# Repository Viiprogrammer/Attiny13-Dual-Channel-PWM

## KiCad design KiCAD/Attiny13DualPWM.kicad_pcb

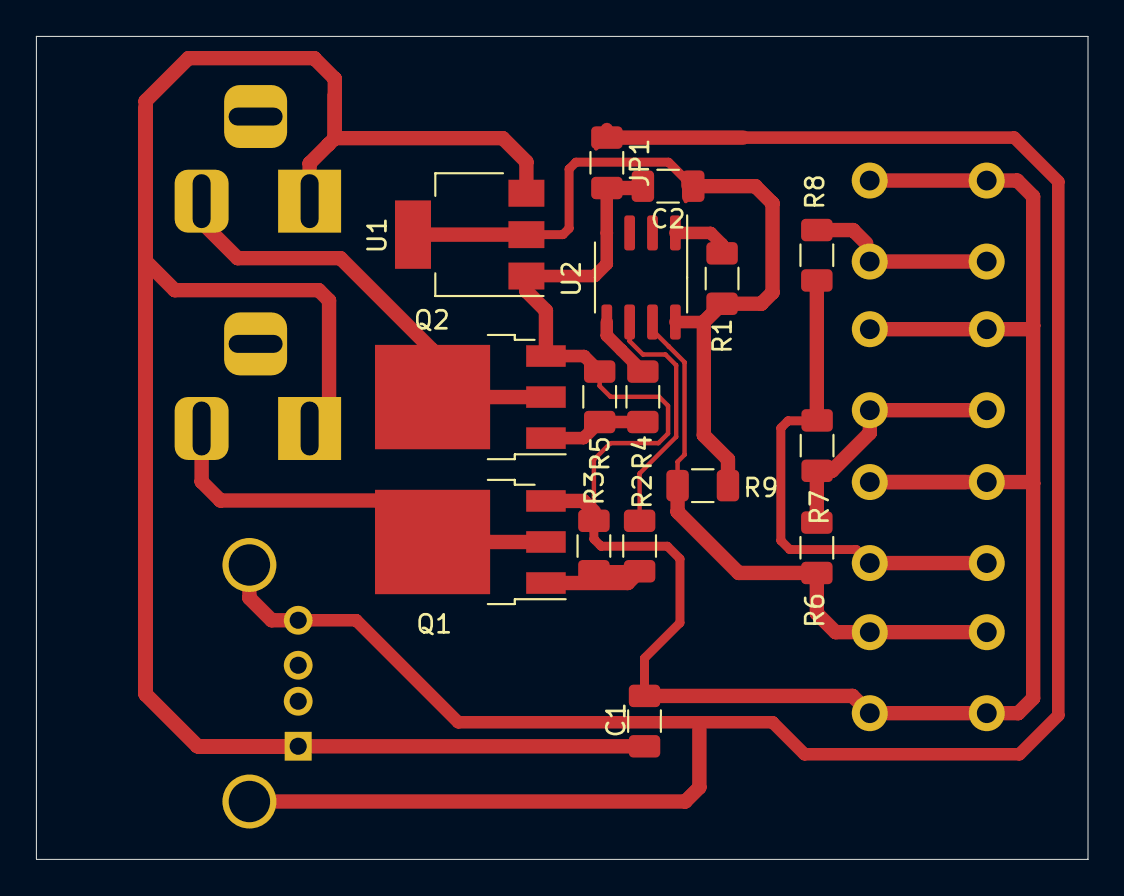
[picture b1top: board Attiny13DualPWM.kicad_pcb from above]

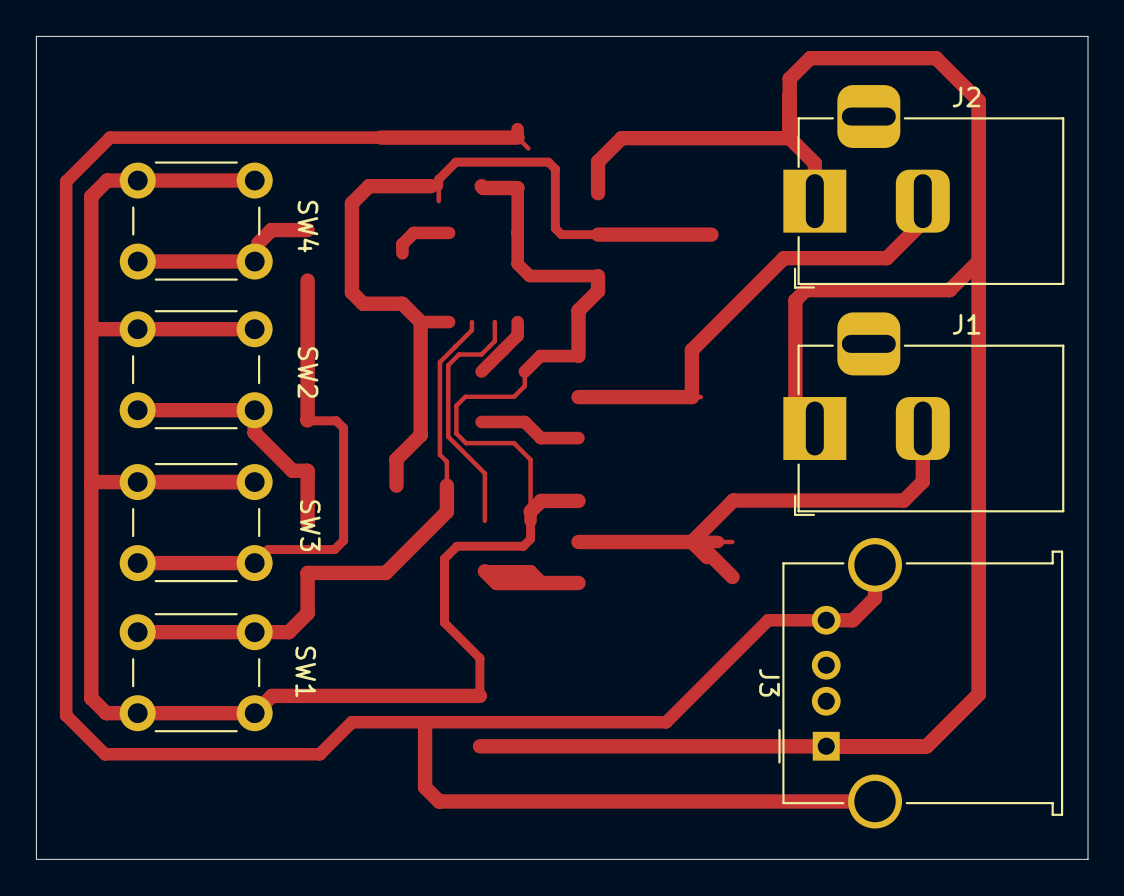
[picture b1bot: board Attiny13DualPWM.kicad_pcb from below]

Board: 2 copper layers, 58.4 x 45.7 mm, 23 parts (7 on the bottom side), 15 nets.

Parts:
C1, C2: C; C_1206_3216Metric
J1, J2: Barrel_Jack_Switch; BarrelJack_Horizontal
J3: USB_A; USB_A_Molex_67643_Horizontal
JP1: Jumper_2_Bridged; R_1206_3216Metric
Q1, Q2: IRLR024NPBF; TO-252-3_TabPin2
R1: 10k; R_1206_3216Metric
R2, R3, R4, R5: 1k; R_1206_3216Metric
R6, R7, R8, R9: 4.7k; R_1206_3216Metric
SW1, SW2, SW3, SW4: SW_Push_Dual_x2; SW_PUSH_6mm
U1: AMS1117; SOT-223-3_TabPin2
U2: ATtiny13A-SSU; SOIC-8_3.9x4.9mm_P1.27mm

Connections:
+3V3: C2.1, R1.2, R9.1, U1.2, U2.8
GND: C1.2, C2.2, JP1.2, Q1.3, Q2.3, R3.2, R5.2, SW1.2, SW2.2, SW3.2, SW4.2, U1.1, U2.4
unnamed: J1.2, Q1.2
unnamed: J2.2, Q2.2
unnamed: J3.4, J3.5, JP1.1
unnamed: Q1.1, R2.2, R3.1
unnamed: Q2.1, R4.2, R5.1
unnamed: R1.1, U2.1
unnamed: R2.1, U2.6
unnamed: R4.1, U2.5
unnamed: R6.1, R9.2, SW1.1, U2.7
unnamed: R6.2, R7.1, SW2.1
unnamed: R7.2, R8.2, SW3.1
unnamed: R8.1, SW4.1
VCC: C1.1, J1.1, J2.1, J3.1, U1.3

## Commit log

2020-08-06 Add files
2020-08-18 ADC values && Delay && EEPROM ready
    Changed the ADC buttons values. Added EEPROM readiness check
2020-08-18 Add Proteus 8.7 Simulation project
2020-09-16 KiCAD files
2021-06-27 Remove trash
